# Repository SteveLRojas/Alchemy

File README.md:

# Alchemy
Reusable microcontroller module with USB

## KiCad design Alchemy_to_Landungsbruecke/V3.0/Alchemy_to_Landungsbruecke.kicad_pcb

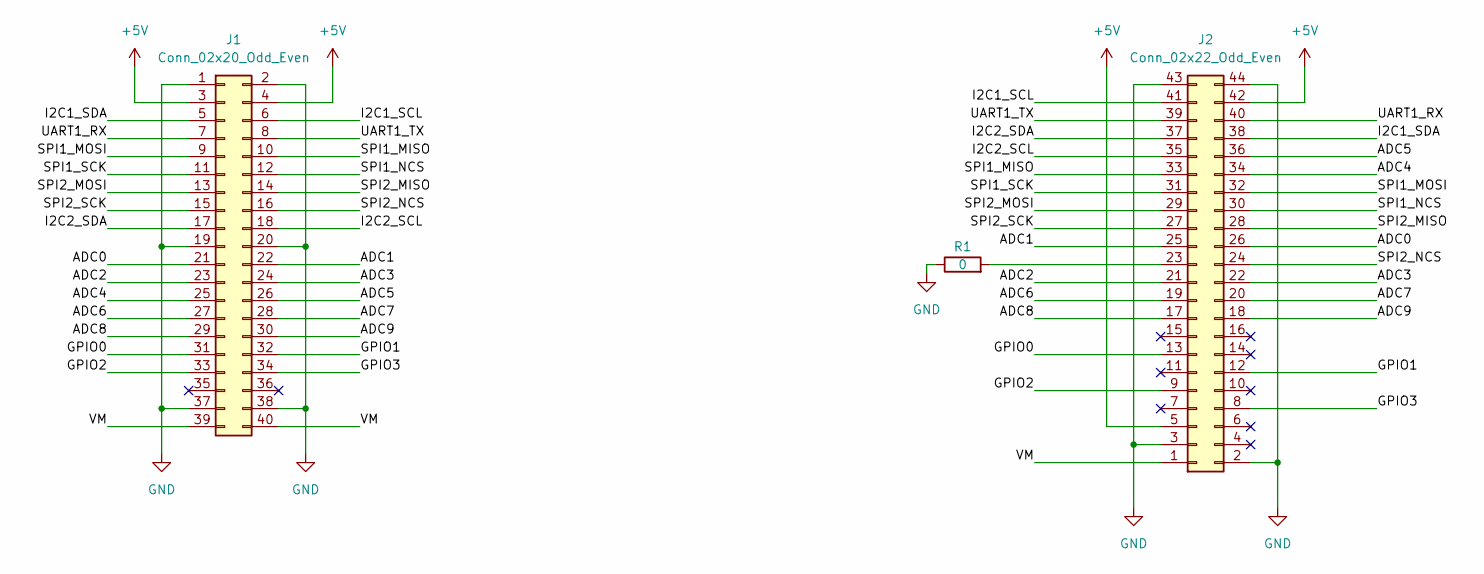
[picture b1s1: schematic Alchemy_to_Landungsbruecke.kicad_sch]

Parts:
J1: Conn_02x20_Odd_Even; con_Alchemy_mirrored
J2: Conn_02x22_Odd_Even; PinHeader_2x22_P2.54mm_Vertical
R1: 0; R_0805_2012Metric

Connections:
+5V: J1.3, J1.4, J2.5, J2.42
/ADC0: J1.21, J2.26
/ADC1: J1.22, J2.25
/ADC2: J1.23, J2.21
/ADC3: J1.24, J2.22
/ADC4: J1.25, J2.34
/ADC5: J1.26, J2.36
/ADC6: J1.27, J2.19
/ADC7: J1.28, J2.20
/ADC8: J1.29, J2.17
/ADC9: J1.30, J2.18
/GPIO0: J1.31, J2.13
/GPIO1: J1.32, J2.12
/GPIO2: J1.33, J2.9
/GPIO3: J1.34, J2.8
/I2C1_SCL: J1.6, J2.41
/I2C1_SDA: J1.5, J2.38
/I2C2_SCL: J1.18, J2.35
/I2C2_SDA: J1.17, J2.37
/SPI1_MISO: J1.10, J2.33
/SPI1_MOSI: J1.9, J2.32
/SPI1_NCS: J1.12, J2.30
/SPI1_SCK: J1.11, J2.31
/SPI2_MISO: J1.14, J2.28
/SPI2_MOSI: J1.13, J2.29
/SPI2_NCS: J1.16, J2.24
/SPI2_SCK: J1.15, J2.27
/UART1_RX: J1.7, J2.40
/UART1_TX: J1.8, J2.39
/VM: J1.39, J1.40, J2.1
GND: J1.1, J1.2, J1.19, J1.20, J1.37, J1.38, J2.2, J2.3, J2.43, J2.44, R1.1
unnamed: J2.23, R1.2

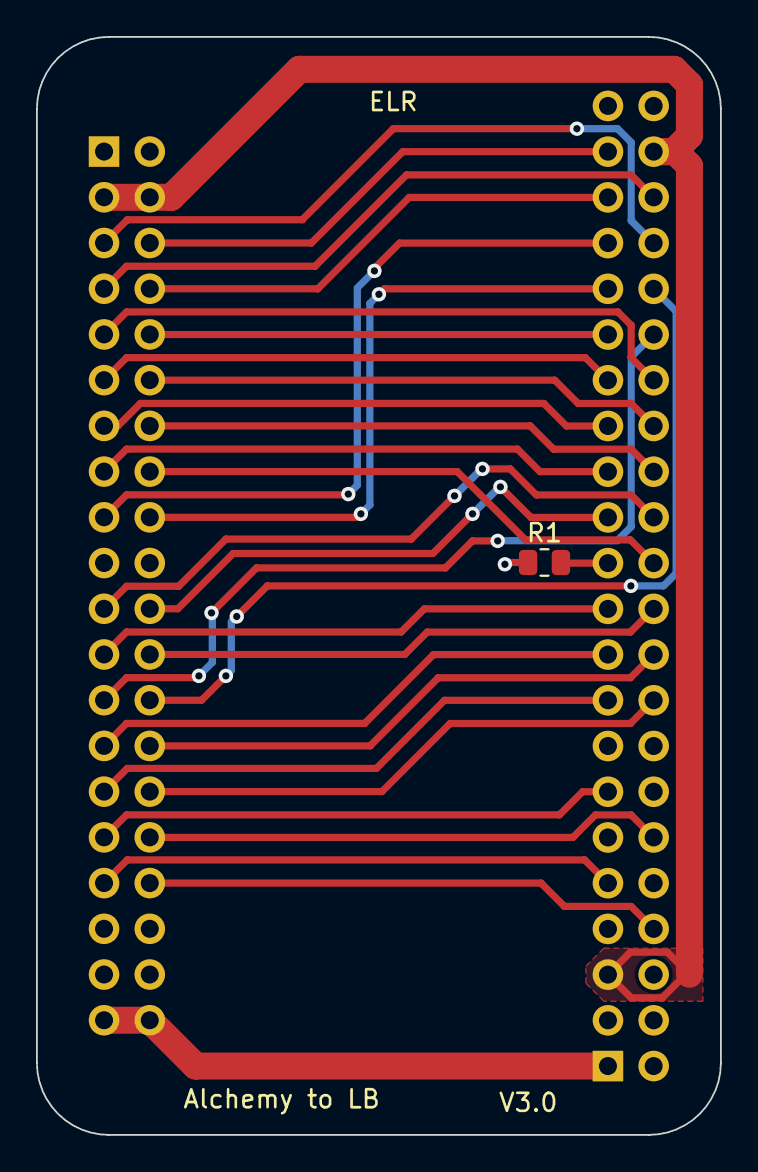
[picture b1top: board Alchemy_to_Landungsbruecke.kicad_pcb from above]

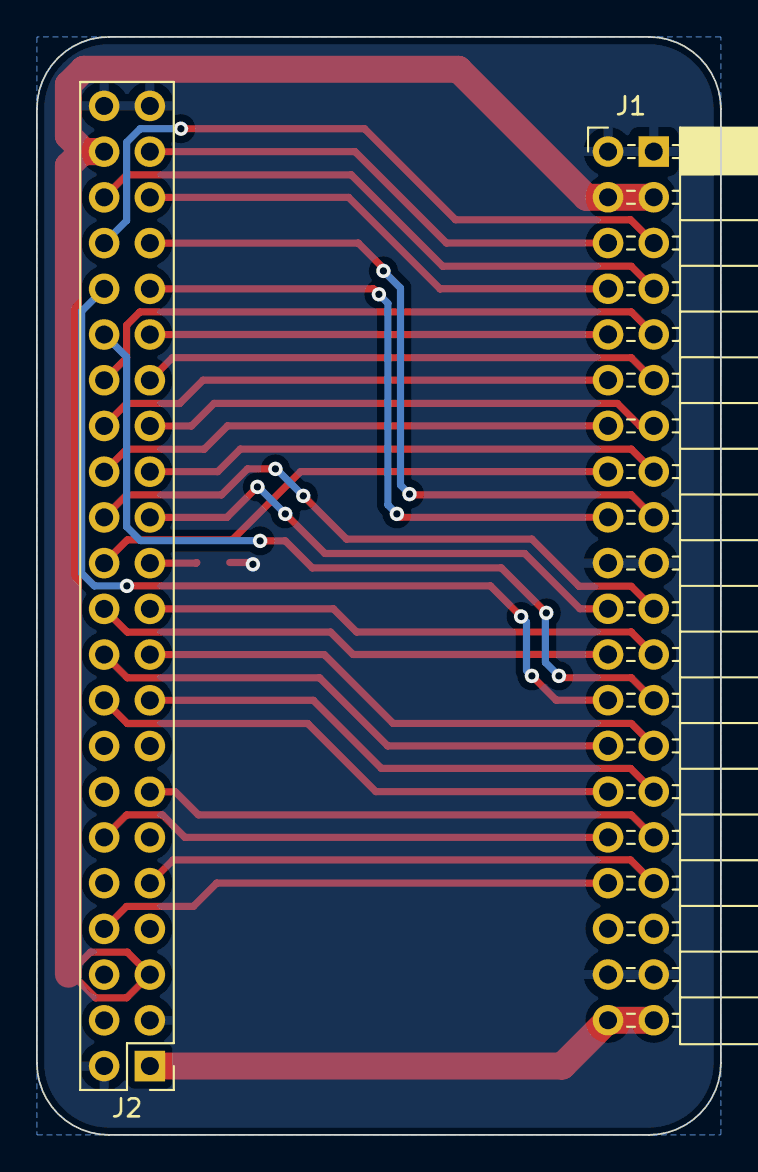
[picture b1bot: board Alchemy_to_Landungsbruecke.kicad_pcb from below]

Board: 2 copper layers, 38.0 x 61.0 mm, 3 parts (2 on the bottom side), 32 nets.

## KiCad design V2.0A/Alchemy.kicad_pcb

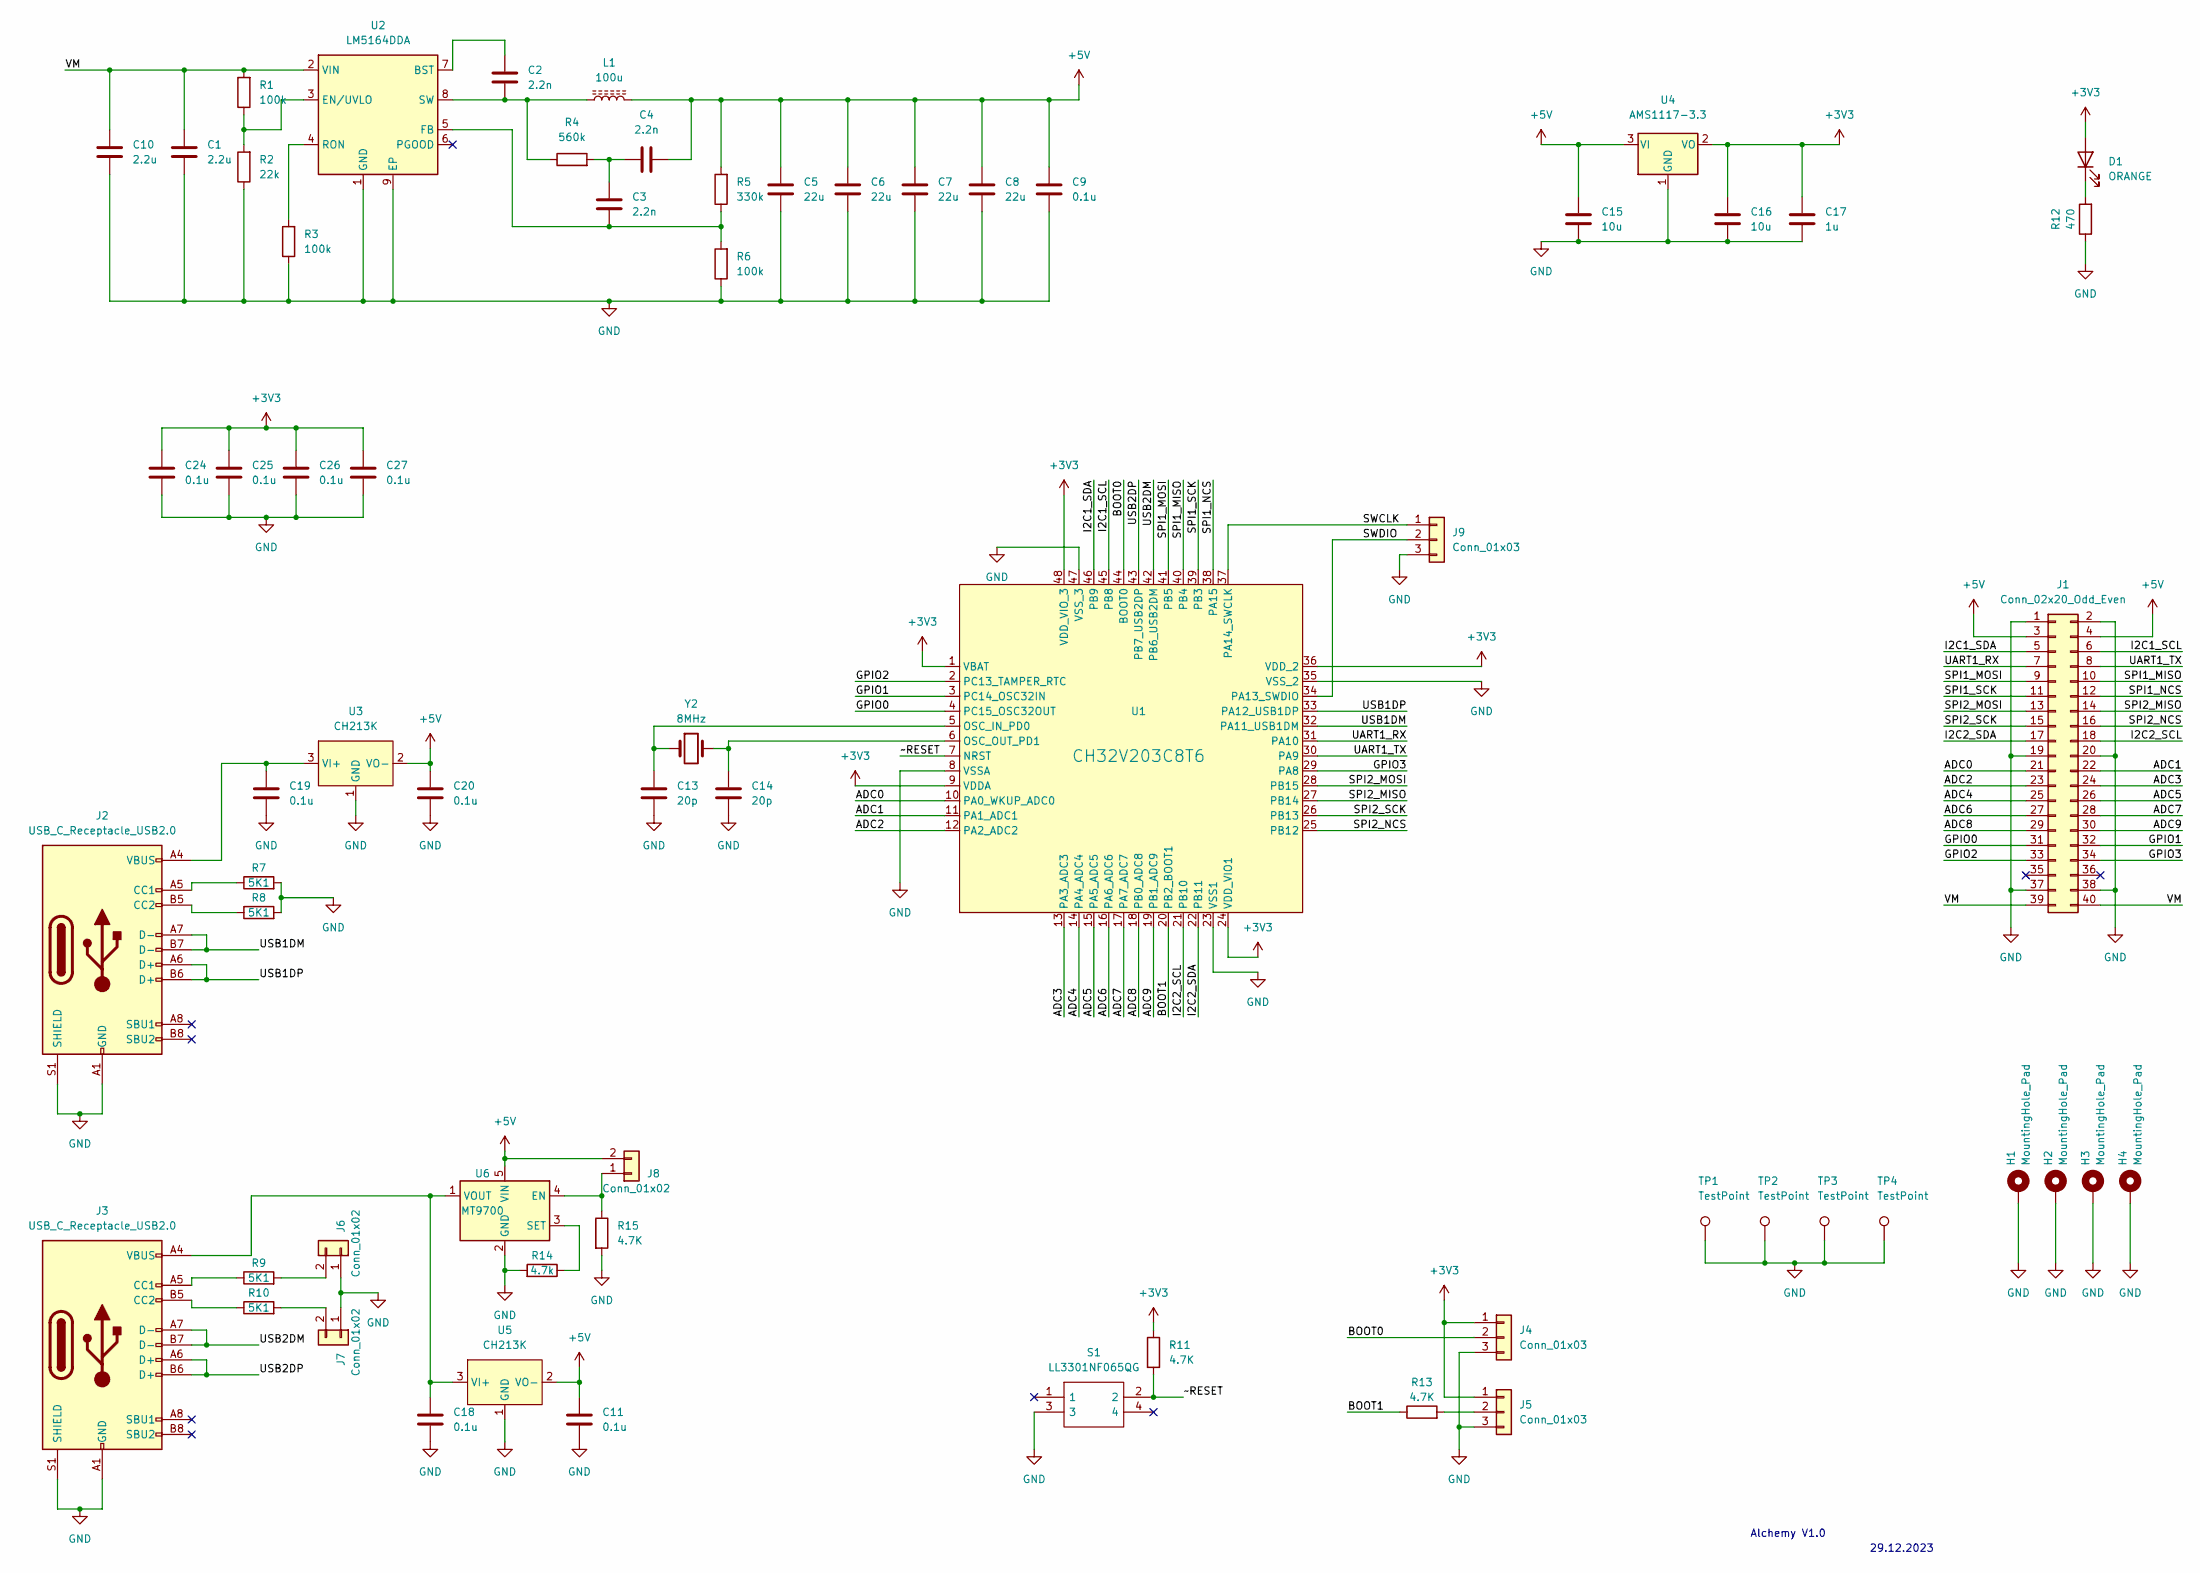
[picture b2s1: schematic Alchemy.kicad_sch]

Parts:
C1, C10: 2.2u; C_1206_3216Metric
C2, C3, C4: 2.2n; C_0805_2012Metric
C5, C6, C7, C8: 22u; C_1206_3216Metric
C9, C11, C18, C19, C20, C24, C25, C26, C27: 0.1u; C_0805_2012Metric
C13, C14: 20p; C_0805_2012Metric
C15, C16: 10u; C_1206_3216Metric
C17: 1u; C_0805_2012Metric
D1: ORANGE; LED_0805_2012Metric
H1, H2, H3, H4: MountingHole_Pad; MountingHole_3.2mm_M3_Pad
J1: Conn_02x20_Odd_Even; PinHeader_2x20_P2.54mm_Horizontal
J2, J3: USB_C_Receptacle_USB2.0; USB_C_Receptacle_HRO_TYPE-C-31-M-12
J4, J5, J9: Conn_01x03; PinHeader_1x03_P2.54mm_Vertical
J6, J7, J8: Conn_01x02; PinHeader_1x02_P2.54mm_Vertical
L1: 100u; L_10.4x10.4_H4.8
R1, R3, R6: 100k; R_0805_2012Metric
R2: 22k; R_0805_2012Metric
R4: 560k; R_0805_2012Metric
R5: 330k; R_0805_2012Metric
R7, R8, R9, R10: 5K1; R_0805_2012Metric
R11, R13, R15: 4.7K; R_0805_2012Metric
R12: 470; R_0805_2012Metric
R14: 4.7k; R_0805_2012Metric
S1: LL3301NF065QG; Mouser Part Number 612-LL3301NF065QG
TP1, TP2, TP3, TP4: TestPoint; TestPoint_Loop_D2.50mm_Drill1.0mm
U1: CH32V203C8T6; CH32V203C8T6_LQFP-48_7x7mm_P0.5mm
U2: LM5164DDA; HSOP-8-1EP_3.9x4.9mm_P1.27mm_EP2.41x3.1mm_ThermalVias
U3, U5: CH213K; SOT-23
U4: AMS1117-3.3; SOT-223-3_TabPin2
U6: MT9700; SOT-23-5
Y2: 8MHz; Crystal_SMD_HC49-SD

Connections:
+3V3: C16.1, C17.1, C24.1, C25.1, C26.1, C27.1, D1.2 (A), J4.1, J5.1, R11.1, U1.1 (VBAT), U1.9 (VDDA), U1.24 (VDD_VIO1), U1.36 (VDD_2), U1.48 (VDD_VIO_3), U4.2 (VO)
+5V: C4.2, C5.2, C6.2, C7.2, C8.2, C9.2, C11.1, C15.1, C20.1, J1.3, J1.4, J8.2, L1.2, R5.2, U3.2 (VO-), U4.3 (VI), U5.2 (VO-), U6.5 (VIN)
/ADC0: J1.21, U1.10 (PA0_WKUP_ADC0)
/ADC1: J1.22, U1.11 (PA1_ADC1)
/ADC2: J1.23, U1.12 (PA2_ADC2)
/ADC3: J1.24, U1.13 (PA3_ADC3)
/ADC4: J1.25, U1.14 (PA4_ADC4)
/ADC5: J1.26, U1.15 (PA5_ADC5)
/ADC6: J1.27, U1.16 (PA6_ADC6)
/ADC7: J1.28, U1.17 (PA7_ADC7)
/ADC8: J1.29, U1.18 (PB0_ADC8)
/ADC9: J1.30, U1.19 (PB1_ADC9)
/BOOT0: J4.2, U1.44 (BOOT0)
/BOOT1: R13.1, U1.20 (PB2_BOOT1)
/GPIO0: J1.31, U1.4 (PC15_OSC32OUT)
/GPIO1: J1.32, U1.3 (PC14_OSC32IN)
/GPIO2: J1.33, U1.2 (PC13_TAMPER_RTC)
/GPIO3: J1.34, U1.29 (PA8)
/I2C1_SCL: J1.6, U1.45 (PB8)
/I2C1_SDA: J1.5, U1.46 (PB9)
/I2C2_SCL: J1.18, U1.21 (PB10)
/I2C2_SDA: J1.17, U1.22 (PB11)
/SPI1_MISO: J1.10, U1.40 (PB4)
/SPI1_MOSI: J1.9, U1.41 (PB5)
/SPI1_NCS: J1.12, U1.38 (PA15)
/SPI1_SCK: J1.11, U1.39 (PB3)
/SPI2_MISO: J1.14, U1.27 (PB14)
/SPI2_MOSI: J1.13, U1.28 (PB15)
/SPI2_NCS: J1.16, U1.25 (PB12)
/SPI2_SCK: J1.15, U1.26 (PB13)
/SWCLK: J9.1, U1.37 (PA14_SWCLK)
/SWDIO: J9.2, U1.34 (PA13_SWDIO)
/UART1_RX: J1.7, U1.31 (PA10)
/UART1_TX: J1.8, U1.30 (PA9)
/USB1DM: J2.A7 (D-), J2.B7 (D-), U1.32 (PA11_USB1DM)
/USB1DP: J2.A6 (D+), J2.B6 (D+), U1.33 (PA12_USB1DP)
/USB2DM: J3.A7 (D-), J3.B7 (D-), U1.42 (PB6_USB2DM)
/USB2DP: J3.A6 (D+), J3.B6 (D+), U1.43 (PB7_USB2DP)
/VM: C1.2, C10.2, J1.39, J1.40, R1.2, U2.2 (VIN)
/~RESET: R11.2, S1.2, U1.7 (NRST)
GND: C1.1, C5.1, C6.1, C7.1, C8.1, C9.1, C10.1, C11.2, C13.2, C14.2, C15.2, C16.2, C17.2, C18.2, C19.2, C20.2, C24.2, C25.2, C26.2, C27.2, H1.1, H2.1, H3.1, H4.1, J1.1, J1.2, J1.19, J1.20, J1.37, J1.38, J2.A1 (GND), J2.A12 (GND), J2.B1 (GND), J2.B12 (GND), J2.S1 (SHIELD), J3.A1 (GND), J3.A12 (GND), J3.B1 (GND), J3.B12 (GND), J3.S1 (SHIELD), J4.3, J5.3, J6.1, J7.1, J9.3, R2.1, R3.1, R6.1, R7.2, R8.2, R12.1, R14.2, R15.2, S1.3, TP1.1, TP2.1, TP3.1, TP4.1, U1.8 (VSSA), U1.23 (VSS1), U1.35 (VSS_2), U1.47 (VSS_3), U2.1 (GND), U2.9 (EP), U3.1 (GND), U4.1 (GND), U5.1 (GND), U6.2 (GND)
unnamed: C2.1, U2.7 (BST)
unnamed: C2.2, L1.1, R4.1, U2.8 (SW)
unnamed: C3.1, R5.1, R6.2, U2.5 (FB)
unnamed: C3.2, C4.1, R4.2
unnamed: C13.1, U1.5 (OSC_IN_PD0), Y2.1
unnamed: C14.1, U1.6 (OSC_OUT_PD1), Y2.2
unnamed: C18.1, J3.A4 (VBUS), J3.A9 (VBUS), J3.B4 (VBUS), J3.B9 (VBUS), U5.3 (VI+), U6.1 (VOUT)
unnamed: C19.1, J2.A4 (VBUS), J2.A9 (VBUS), J2.B4 (VBUS), J2.B9 (VBUS), U3.3 (VI+)
unnamed: D1.1 (K), R12.2
unnamed: J2.A5 (CC1), R7.1
unnamed: J2.B5 (CC2), R8.1
unnamed: J3.A5 (CC1), R9.1
unnamed: J3.B5 (CC2), R10.1
unnamed: J5.2, R13.2
unnamed: J8.1, R15.1, U6.4 (EN)
unnamed: R1.1, R2.2, U2.3 (EN/UVLO)
unnamed: R3.2, U2.4 (RON)
unnamed: J6.2, R9.2
unnamed: J7.2, R10.2
unnamed: R14.1, U6.3 (SET)

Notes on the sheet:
29.12.2023
Alchemy V1.0

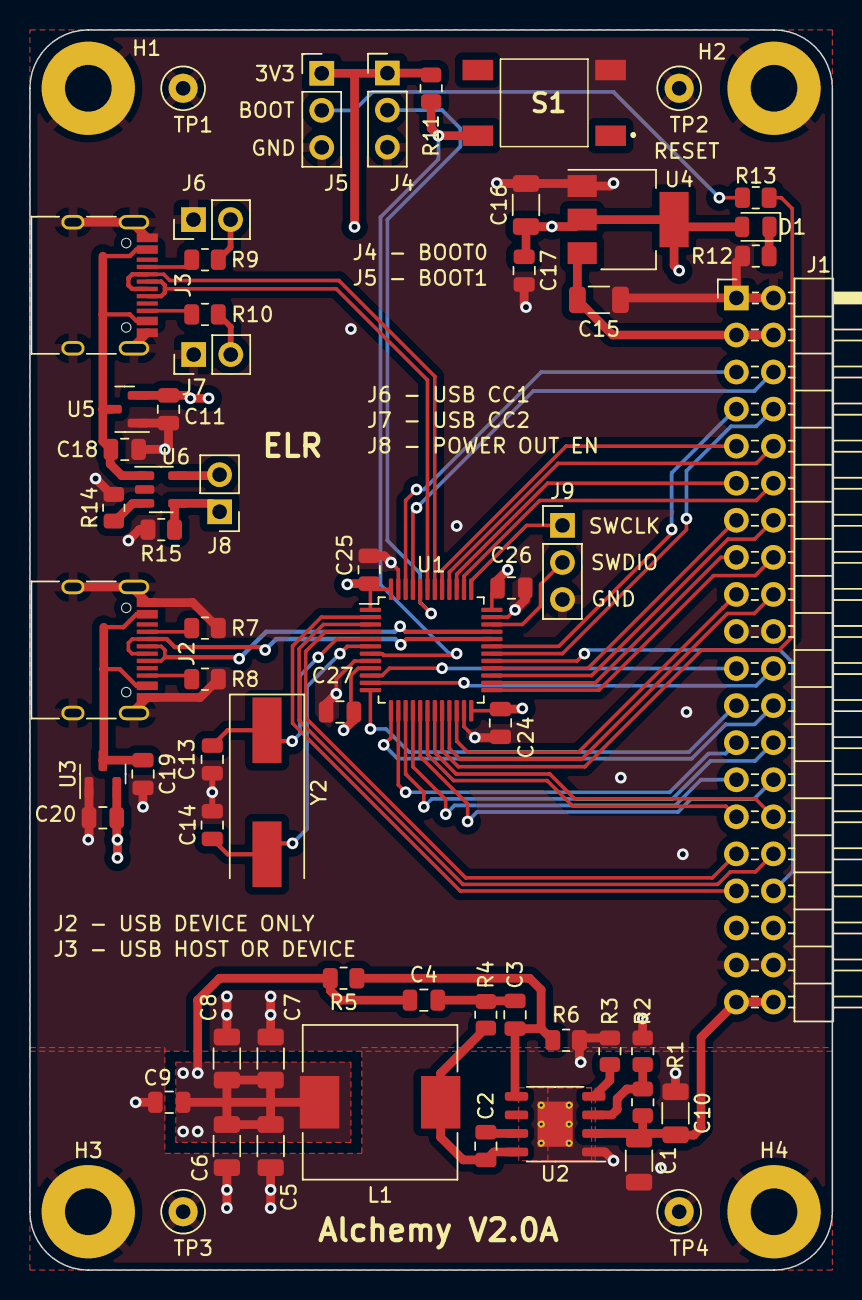
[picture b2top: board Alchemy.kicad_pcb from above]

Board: 4 copper layers, 55.0 x 85.0 mm, 65 parts (0 on the bottom side), 61 nets.

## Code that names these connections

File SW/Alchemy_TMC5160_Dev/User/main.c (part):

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// DIAG0 = PA0
// DIAG1 = PA1
// DRV_EN = PA2
// USART1_TX = PA9
// USART1_RX = PA10
// UDM = PA11
// UDP = PA12
// SPI1_NCS = PA15
// SPI1_SCK = PB3
// SPI1_MISO = PB4
// SPI1_MOSI = PB5
// LED3 = PB6
// LED2 = PB7
// LED1 = PB8
// LED0 = PB9
// ENCN = PB11
// ENCA = PB12
// ENCB = PB13
// DIR = PB14
// STEP = PB15

//FW registers
// 0x7FFF:	Reserved for Interface Mode
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
	gpio_set_mode(GPIOA, GPIO_DIR_SPD_OUT_50MHZ | GPIO_MODE_AFIO_PP, GPIO_PIN_9);	//USART1_TX
	gpio_set_mode(GPIOA, GPIO_DIR_SPD_OUT_50MHZ | GPIO_MODE_PULL_IN, GPIO_PIN_0 | GPIO_PIN_1 | GPIO_PIN_10);	//DIAG0, DIAG1, USART1_RX
	gpio_set_mode(GPIOA, GPIO_DIR_SPD_OUT_50MHZ | GPIO_MODE_PP_OUT, GPIO_PIN_2 | GPIO_PIN_15);	//DRV_EN, SPI1_NCS

	gpio_set_mode(GPIOB, GPIO_DIR_SPD_OUT_50MHZ | GPIO_MODE_AFIO_PP, GPIO_PIN_3 | GPIO_PIN_5);	//SPI1_SCK, SPI1_MOSI
	gpio_set_mode(GPIOB, GPIO_DIR_SPD_IN | GPIO_MODE_PULL_IN, GPIO_PIN_4);			//SPI1_MISO
	gpio_set_mode(GPIOB, GPIO_DIR_SPD_OUT_50MHZ | GPIO_MODE_PP_OUT, GPIO_PIN_6 | GPIO_PIN_7 | GPIO_PIN_8 | GPIO_PIN_9);	//LED3, LED2, LED1, LED0

	gpio_set_pin(GPIOA, GPIO_PIN_0 | GPIO_PIN_1 | GPIO_PIN_10 | GPIO_PIN_2 | GPIO_PIN_15);	//pull-up DIAG0, DIAG1 USART1_RX, set DRV_EN, SPI1_NCS high
	gpio_set_pin(GPIOB, GPIO_PIN_4 | GPIO_PIN_6 | GPIO_PIN_7 | GPIO_PIN_8 | GPIO_PIN_9);	//pull-up SPI1_MISO, set LED3, LED2, LED1, LED0

	delay_init();
	uart_init(USART1, 115200);
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
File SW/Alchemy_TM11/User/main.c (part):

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// USART2_TX = PA2
// USART2_RX = PA3
// IREF_R3 = PA5
// NDRV_EN = PA8
// USART1_TX = PA9
// USART1_RX = PA10
// UDM = PA11
// UDP = PA12
// SPI1_NCS = PA15
// UART_EN = PB0
// SPI1_SCK = PB3
// SPI1_MISO = PB4
// SPI1_MOSI = PB5
// IREF_R2 = PB10
// NSLEEP = PC15

//Control flags:
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	rcc_apb2_clk_enable(RCC_AFIOEN | RCC_IOPAEN | RCC_IOPBEN | RCC_IOPCEN | RCC_TIM1EN | RCC_SPI1EN | RCC_USART1EN);
	rcc_apb1_clk_enable(RCC_TIM2EN | RCC_USBEN | RCC_USART2EN);

	gpio_set_mode(GPIOA, GPIO_DIR_SPD_OUT_50MHZ | GPIO_MODE_PP_OUT, GPIO_PIN_1 | GPIO_PIN_5 | GPIO_PIN_8 | GPIO_PIN_15);	//UART_EN, IREF_R3, NDRV_EN, SPI1_NCS
	gpio_set_mode(GPIOA, GPIO_DIR_SPD_OUT_50MHZ | GPIO_MODE_AFIO_PP, GPIO_PIN_2 | GPIO_PIN_9);	//USART2_TX, USART1_TX
	gpio_set_mode(GPIOA, GPIO_DIR_SPD_OUT_50MHZ | GPIO_MODE_PULL_IN, GPIO_PIN_3 | GPIO_PIN_10);	//USART2_RX, USART1_RX
	gpio_set_mode(GPIOB, GPIO_DIR_SPD_OUT_50MHZ | GPIO_MODE_PP_OUT, GPIO_PIN_0 | GPIO_PIN_10);	//CLK16, IREF_R2
	gpio_set_mode(GPIOB, GPIO_DIR_SPD_OUT_50MHZ | GPIO_MODE_AFIO_PP, GPIO_PIN_3 | GPIO_PIN_5);	//SPI1_SCK, SPI1_MOSI
	gpio_set_mode(GPIOB, GPIO_DIR_SPD_IN | GPIO_MODE_PULL_IN, GPIO_PIN_4);			//SPI1_MISO
	gpio_set_mode(GPIOC, GPIO_DIR_SPD_OUT_2MHZ | GPIO_MODE_PP_OUT, GPIO_PIN_15);	//NSLEEP

	gpio_clear_pin(GPIOA, GPIO_PIN_1 | GPIO_PIN_5);	//CLK16, IREF_R3 low
	gpio_clear_pin(GPIOB, GPIO_PIN_0 | GPIO_PIN_10);	//UART_EN, IREF_R2 low
	gpio_set_pin(GPIOA, GPIO_PIN_8 | GPIO_PIN_15 | GPIO_PIN_3 | GPIO_PIN_10);	//DNRV_EN, SPI1_NCS high, pull-up USART2_RX, USART1_RX
	gpio_set_pin(GPIOB, GPIO_PIN_4);	//pull-up SPI1_MISO
	gpio_set_pin(GPIOC, GPIO_PIN_15);	//NSLEEP high

    Delay_Init();
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
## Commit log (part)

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2023-12-29 Created V1.0
2024-01-12 removed backups
2024-01-31 Updated BOM
2024-02-11 deleted backups
2024-02-23 Added firmware for TMC5130 and Nano-FOC
2024-05-14 Added V1.0 schematic PDF
2024-10-17 Updated pinout
2024-11-25 Fixed pinout
2025-02-20 Updated Nano-FOC project with new libraries
2025-04-04 Added RTMI functionality for Nano-FOC
2025-05-10 Added TMC5160_Dev firmware
2025-09-16 Added Alchemy_to_LB V2.0 and V3.0
2025-09-19 Added V2.0A
2025-09-19 Added 0 ohm resistor to GND for LB CLK
2025-09-20 Added V2.0B
2025-09-20 Minor layout fixes
2025-10-10 added BOM for V2.0B
2025-10-12 Fixed error in BOM
2025-10-30 Updated Nano-FOC firmware

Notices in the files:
SW/Alchemy_TM11/User/main.c:
Copyright (C) 2024 Esteban Looser-Rojas.
SW/Alchemy_TMC5160_Dev/User/main.c:
Copyright (C) 2025 Esteban Looser-Rojas.
